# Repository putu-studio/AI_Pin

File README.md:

# AI Pin

A wearable voice assistant built on the Seeed XIAO ESP32-S3 Sense. Hold the button, ask a question out loud, and the answer appears on a small screen, a page at a time.

The pin records your voice and sends it to a relay server that you run on your own computer. The relay turns speech into text, asks an AI assistant, and sends back a short answer sized for the screen.

The Sense board also has a camera, but this project doesn't use it. Only the on-board microphone is needed.

```
  ┌──────────────┐   Wi-Fi + HTTPS    ┌─────────────────────────────┐
  │   AI Pin     │ ─── audio ───────► │  Relay (your computer)      │
  │ ESP32-S3     │                    │  Whisper speech-to-text     │
  │ mic, screen, │ ◄── answer ─────── │  AI assistant + your brain  │
  │ one button   │   (JSON pages)     │  folder of instructions     │
  └──────────────┘                    └─────────────────────────────┘
```

## Features

- One-button control: hold to talk, let go to send, tap to turn pages, hold to clear.
- Speech-to-text with Whisper, in English plus one optional second language (see [Supporting other languages](relay/README.md#supporting-other-languages)).
- Answers are formatted for a 1.69" 240 × 280 display: 21 characters per line, 11 lines per page.
- Remembers things you ask it to remember, in a local folder you control.
- Web search and live weather (Open-Meteo, no API key) when a question needs current information.
- Wi-Fi set up over USB serial on first boot, then saved to flash.
- Custom carrier PCB with LiPo charging over USB-C.

## Repository layout

| Folder | What's inside |
|---|---|
| [`firmware/`](firmware/) | ESP-IDF firmware for the pin |
| [`relay/`](relay/) | Python server that the pin talks to |
| [`brain-template/`](brain-template/) | Starter instructions for the assistant. Copy it and make it your own |
| [`hardware/`](hardware/) | KiCad carrier board, footprints, BOM and Gerbers |

## Quick start

1. **Build the hardware.** Order the carrier board from [`hardware/`](hardware/), or wire a XIAO ESP32-S3 Sense to an ST7789 display and a push button on a breadboard (pins are in [`firmware/main/board.h`](firmware/main/board.h)).
2. **Set up the relay** on a computer that stays on. Follow [`relay/README.md`](relay/README.md). You'll end up with an HTTPS address and a token.
3. **Create your brain folder** by copying [`brain-template/`](brain-template/) to `~/assistant-brain` and editing `CLAUDE.md`.
4. **Flash the firmware.** Copy `firmware/main/secrets.example.h` to `secrets.h`, add the relay address and token, then build and flash. See [`firmware/README.md`](firmware/README.md).

On first boot, open the serial monitor, pick your Wi-Fi network and type its password. The pin remembers it after that.

## Status

In progress. The carrier PCB has been fabricated. Firmware and relay are under active development.

## License

[MIT](LICENSE) for the firmware, relay and hardware design files.

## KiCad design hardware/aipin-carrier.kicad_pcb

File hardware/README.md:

# AI Pin carrier board

A two-layer carrier PCB for the Seeed XIAO ESP32-S3 Sense that adds everything the pin needs to run on a battery: LiPo charging over USB-C, a power switch, a button and the display connector.

Designed in KiCad 10. Open `aipin-carrier.kicad_pro`.

## What's on the board

| Block | Details |
|---|---|
| Charger | TP4056, R<sub>PROG</sub> = 2.4 kΩ for about 500 mA, suited to an 1100 mAh LiPo |
| USB-C | 5.1 kΩ CC pull-downs so USB-C chargers supply 5 V, TVS diode on VBUS |
| Power path | Battery → charger → slide switch → XIAO |
| Battery sense | Resistor divider into an ADC pin |
| User input | One push button |
| Display | 1.69" ST7789 module (30 × 47 mm) |

## Files

| Path | Contents |
|---|---|
| `aipin-carrier.kicad_sch` | Schematic |
| `aipin-carrier.kicad_pcb` | Board layout |
| `lib/aipin.pretty/` | Custom footprints (switches and buttons) |
| `production/` | Gerbers and drill files (`aipin-carrier.zip`), BOM, pick-and-place and netlist |

## Ordering

The `production/` files were generated with the KiCad Fabrication Toolkit plugin and are ready to upload to [JLCPCB](https://jlcpcb.com). Upload `aipin-carrier.zip` for the bare board. For assembly, add `bom.csv` and `positions.csv`.

Before ordering, check that every BOM line's LCSC part number matches the value in the schematic.

## Reference

- [XIAO ESP32-S3 Sense documentation](https://wiki.seeedstudio.com/xiao_esp32s3_getting_started/) (pinout and schematic)

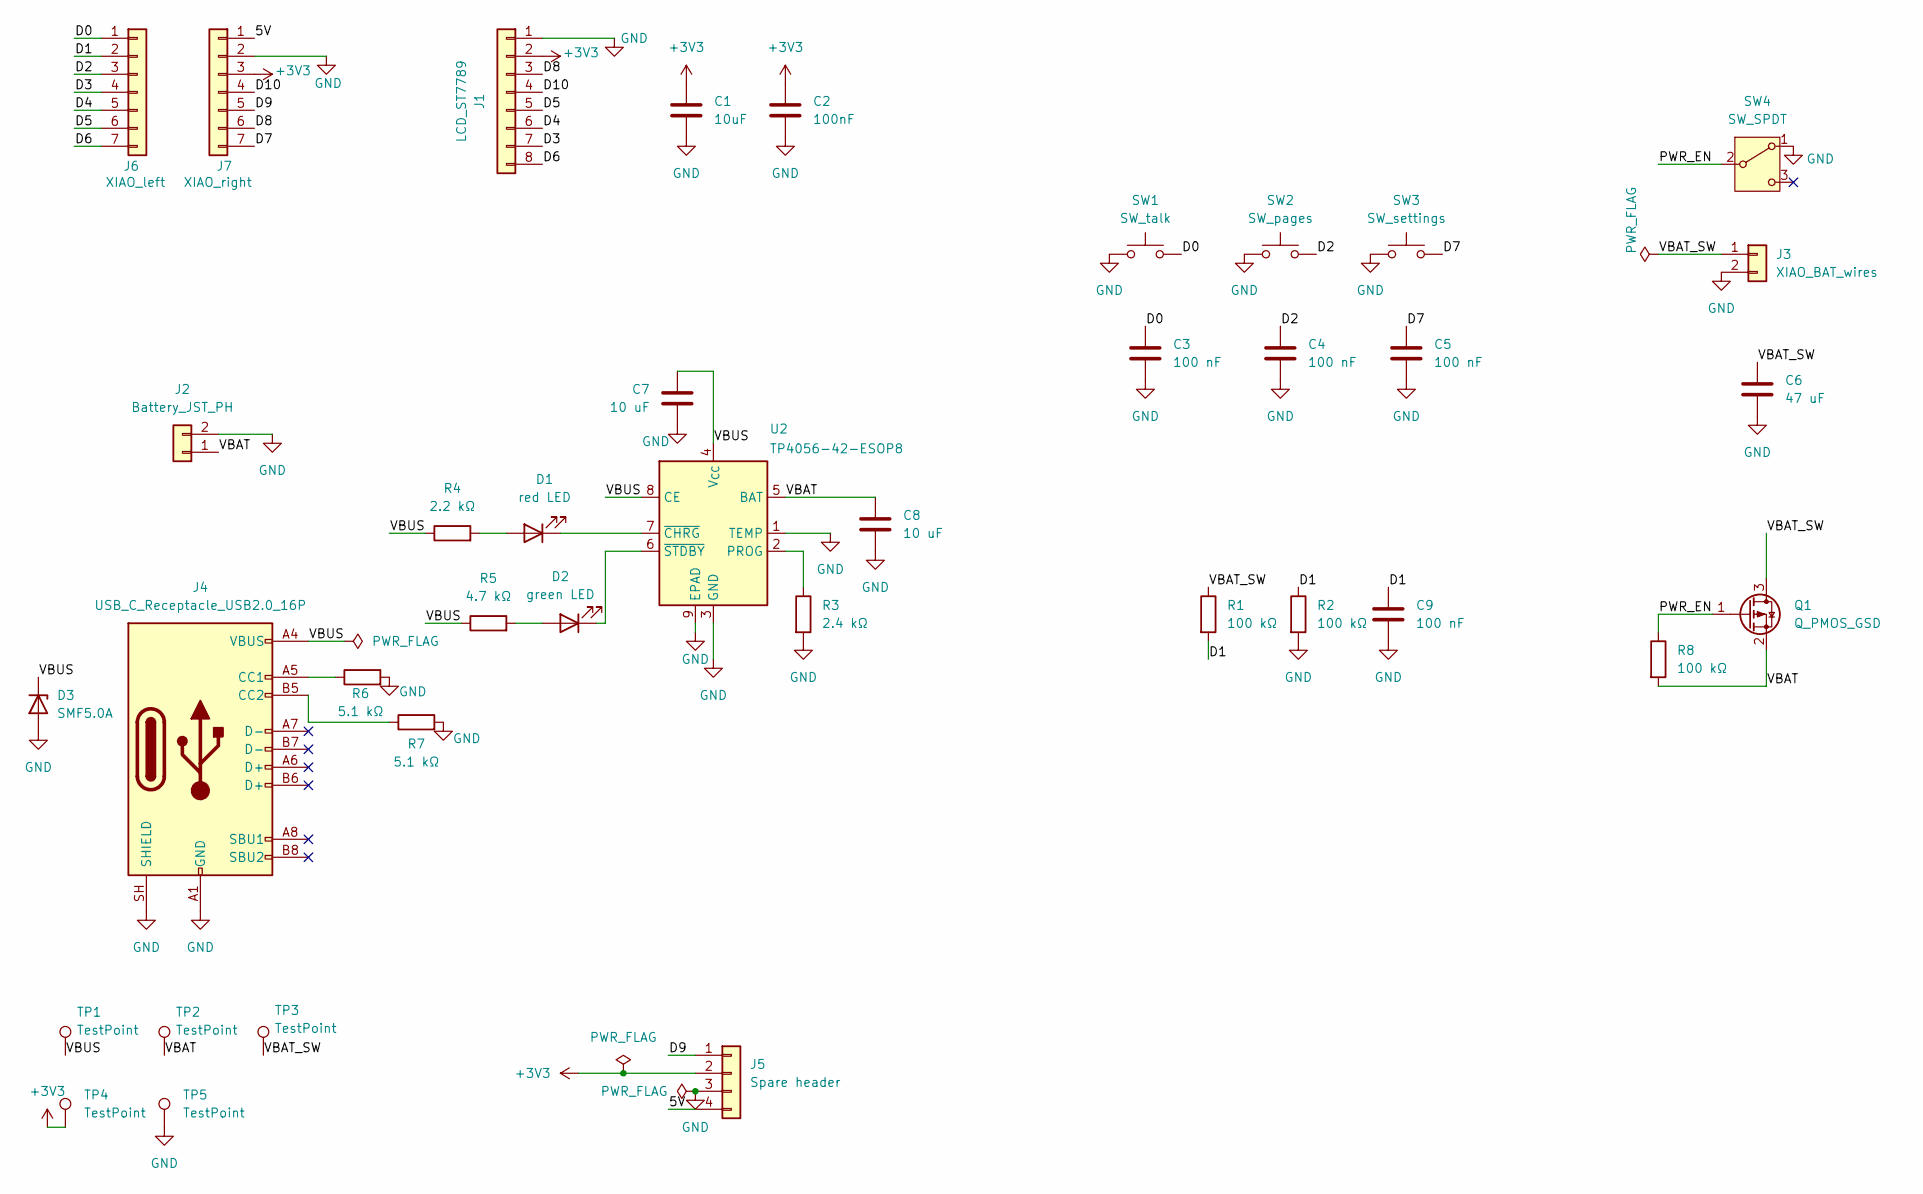
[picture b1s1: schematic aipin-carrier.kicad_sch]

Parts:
C1: 10uF; C_0603_1608Metric; LCSC C19702
C2: 100nF; C_0603_1608Metric; LCSC C14663
C3, C4, C5, C9: 100 nF; C_0603_1608Metric; LCSC C14663
C6: 47 uF; C_1206_3216Metric; LCSC C96123
C7, C8: 10 uF; C_0805_2012Metric; LCSC C15850
D1: red LED; LED_0603_1608Metric; LCSC C2286
D2: green LED; LED_0603_1608Metric; LCSC C84267
D3: SMF5.0A; D_SOD-123F; LCSC C284108
J1: LCD_ST7789; PinSocket_1x08_P2.54mm_Vertical
J2: Battery_JST_PH; JST_PH_S2B-PH-K_1x02_P2.00mm_Horizontal
J3: XIAO_BAT_wires; PinHeader_1x02_P2.54mm_Vertical
J4: USB_C_Receptacle_USB2.0_16P; USB_C_Receptacle_HRO_TYPE-C-31-M-12; LCSC C165948
J5: Spare header; PinHeader_1x04_P2.54mm_Vertical
J6: XIAO_left; PinSocket_1x07_P2.54mm_Vertical
J7: XIAO_right; PinSocket_1x07_P2.54mm_Vertical
Q1: Q_PMOS_GSD; SOT-23; LCSC C15127
R1, R2, R8: 100 kΩ; R_0603_1608Metric; LCSC C25803
R3: 2.4 kΩ; R_0603_1608Metric; LCSC C22940
R4: 2.2 kΩ; R_0603_1608Metric; LCSC C4190
R5: 4.7 kΩ; R_0603_1608Metric; LCSC C23162
R6, R7: 5.1 kΩ; R_0603_1608Metric; LCSC C23186
SW1: SW_talk; SW_Talk_6x6_TS6635PA; LCSC C55213946
SW2: SW_pages; SW_Side_TS1114S; LCSC C596266
SW3: SW_settings; SW_Side_TS1114S; LCSC C596266
SW4: SW_SPDT; SW_Slide_MSK12C02HB; LCSC C431541
TP1, TP2, TP3, TP4, TP5: TestPoint; TestPoint_Pad_D1.5mm
U2: TP4056-42-ESOP8; SOIC-8-1EP_3.9x4.9mm_P1.27mm_EP2.41x3.3mm; LCSC C16581

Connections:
+3V3: C1.1, C2.1, J1.2, J5.2, J7.3, TP4.1 (1_1)
/5V: J5.4, J7.1
/D0: C3.1, J6.1, SW1.2
/D1: C9.1, J6.2, R1.2, R2.1
/D2: C4.1, J6.3, SW2.2
/D3: J1.7, J6.4
/D4: J1.6, J6.5
/D5: J1.5, J6.6
/D6: J1.8, J6.7
/D7: C5.1, J7.7, SW3.2
/D8: J1.3, J7.6
/D9: J5.1, J7.5
/D10: J1.4, J7.4
/PWR_EN: Q1.1 (G), R8.1, SW4.2 (B)
/VBAT: C8.1, J2.1, Q1.2 (S), R8.2, TP2.1 (1_1), U2.5 (BAT)
/VBAT_SW: C6.1, J3.1, Q1.3 (D), R1.1, TP3.1 (1_1)
/VBUS: C7.1, D3.1 (K), J4.A4 (VBUS), J4.A9 (VBUS), J4.B4 (VBUS), J4.B9 (VBUS), R4.1, R5.1, TP1.1 (1_1), U2.4 (V_{CC}), U2.8 (CE)
GND: C1.2, C2.2, C3.2, C4.2, C5.2, C6.2, C7.2, C8.2, C9.2, D3.2 (A), J1.1, J2.2, J3.2, J4.A1 (GND), J4.A12 (GND), J4.B1 (GND), J4.B12 (GND), J4.SH (SHIELD), J5.3, J7.2, R2.2, R3.2, R6.2, R7.2, SW1.1, SW2.1, SW3.1, SW4.1 (A), TP5.1 (1_1), U2.1 (TEMP), U2.3 (GND), U2.9 (EPAD)
unnamed: D1.2 (A), R4.2
unnamed: D1.1 (K), U2.7 (~CHRG)
unnamed: D2.2 (A), R5.2
unnamed: D2.1 (K), U2.6 (~STDBY)
unnamed: J4.A5 (CC1), R6.1
unnamed: J4.B5 (CC2), R7.1
unnamed: R3.1, U2.2 (PROG)

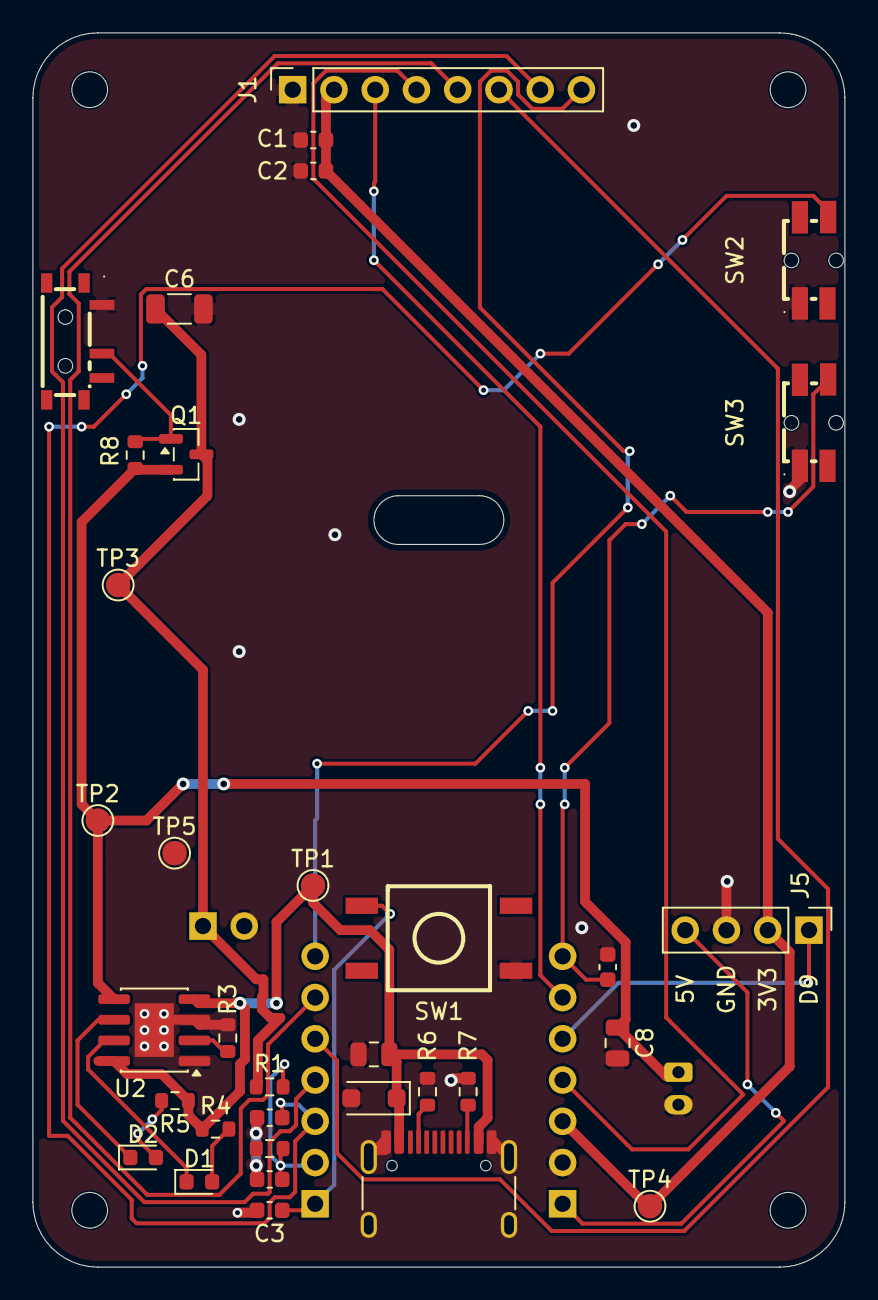
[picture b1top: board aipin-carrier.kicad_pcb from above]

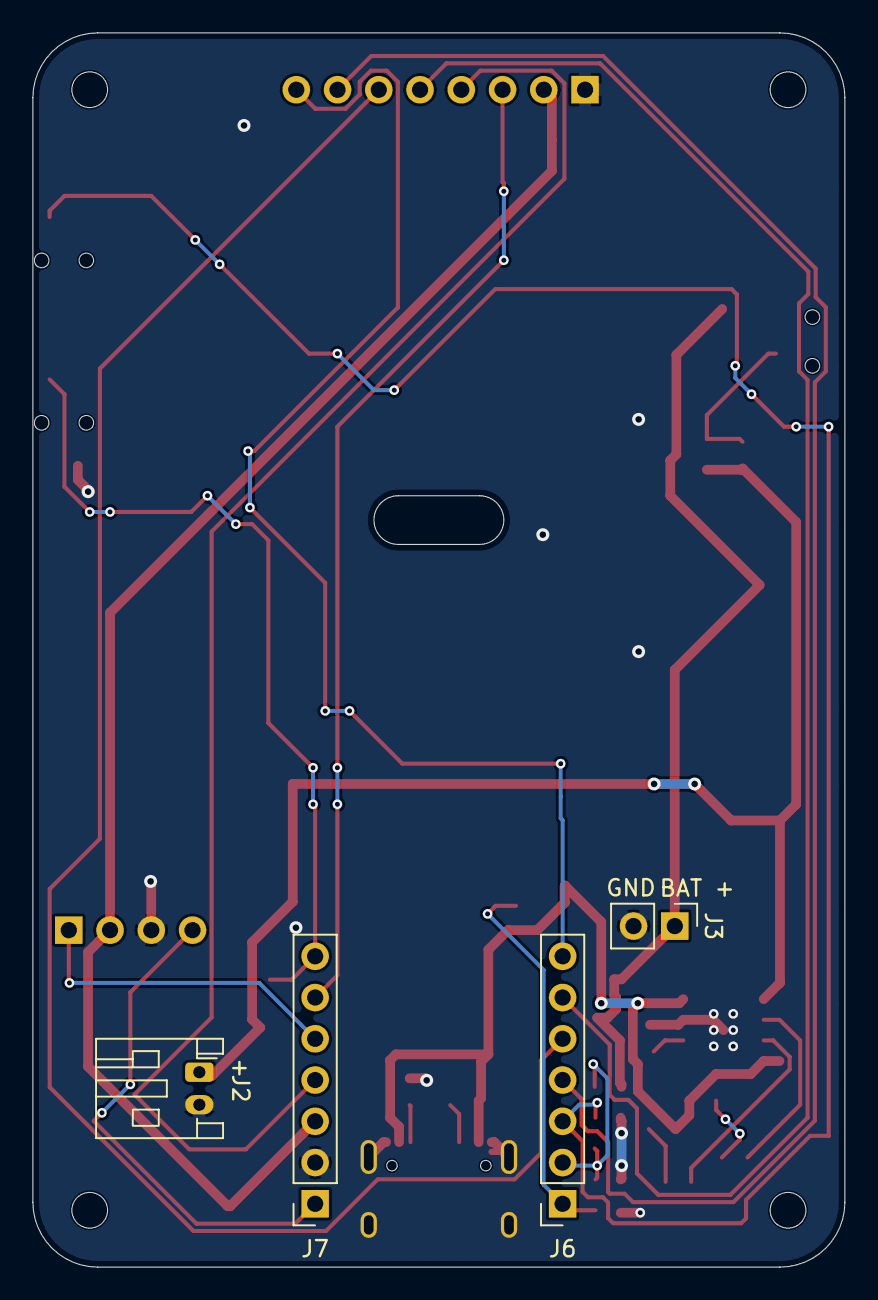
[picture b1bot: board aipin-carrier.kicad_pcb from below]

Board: 2 copper layers, 50.0 x 76.0 mm, 42 parts (4 on the bottom side), 25 nets.

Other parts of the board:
H1, H2, H3, H4: MountingHole_2.2mm_M2
